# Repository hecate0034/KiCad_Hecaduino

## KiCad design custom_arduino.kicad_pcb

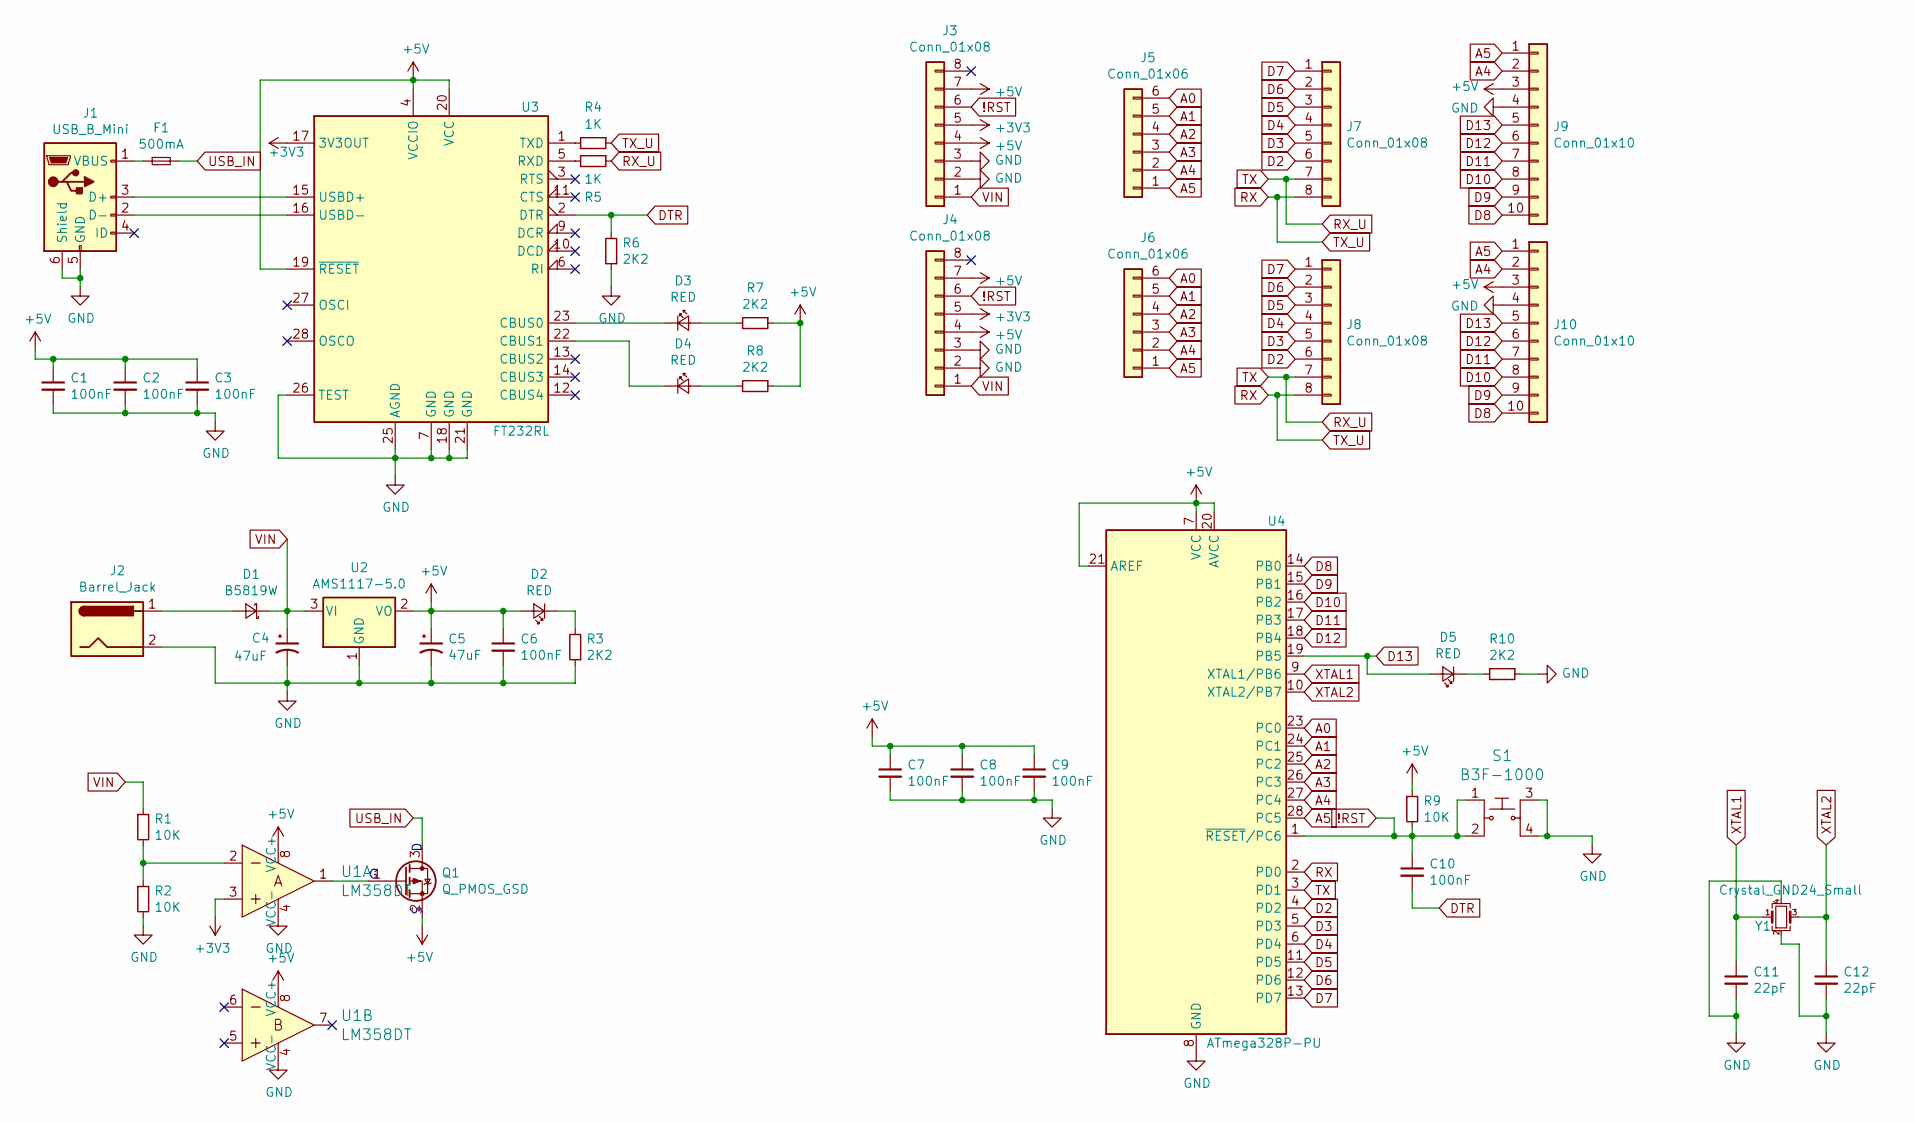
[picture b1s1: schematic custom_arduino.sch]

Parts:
C1, C2, C3, C6, C7, C8, C9, C10: 100nF; C_0402_1005Metric
C4, C5: 47uF; CP_Elec_5x5.4
C11, C12: 22pF; C_0402_1005Metric
D1: B5819W; D_SOD-123
D2, D3, D4, D5: RED; LED_0603_1608Metric
F1: 500mA; Fuse_0603_1608Metric
J1: USB_B_Mini; USB_Mini-B_Lumberg_2486_01_Horizontal
J2: Barrel_Jack; BarrelJack_Horizontal
J3, J4, J7, J8: Conn_01x08; PinSocket_1x08_P2.54mm_Vertical
J5, J6: Conn_01x06; PinSocket_1x06_P2.54mm_Vertical
J9, J10: Conn_01x10; PinSocket_1x10_P2.54mm_Vertical
Q1: Q_PMOS_GSD; SOT-23
R1, R2, R9: 10K; R_0603_1608Metric
R3, R6, R7, R8, R10: 2K2; R_0603_1608Metric
R4, R5: 1K; R_0603_1608Metric
S1: B3F-1000; B3F1002; MPN B3F-1000; Digi-Key_PN SW400-ND
U1: LM358DT; SOIC-8_3.9x4.9mm_P1.27mm; MPN LM358DT; Digi-Key_PN 497-1591-1-ND
U2: AMS1117-5.0; SOT-223-3_TabPin2
U3: FT232RL; SSOP-28_5.3x10.2mm_P0.65mm
U4: ATmega328P-PU; DIP-28_W7.62mm
Y1: Crystal_GND24_Small; Crystal_SMD_3225-4Pin_3.2x2.5mm

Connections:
!RST: C10.1, J3.6, J4.6, R9.2, S1.1, S1.2, U4.1 (~RESET~/PC6)
+3V3: J3.5, J4.5, U1.3, U3.17 (3V3OUT)
+5V: C1.1, C2.1, C3.1, C5.1, C6.1, C7.1, C8.1, C9.1, D2.2 (A), J3.4, J3.7, J4.4, J4.7, J9.3, J10.3, Q1.2 (S), R7.1, R8.1, R9.1, U1.8 (VCC+), U2.2 (VO), U3.4 (VCCIO), U3.19 (~RESET~), U3.20 (VCC), U4.7 (VCC), U4.20 (AVCC), U4.21 (AREF)
A0: J5.6, J6.6, U4.23 (PC0)
A1: J5.5, J6.5, U4.24 (PC1)
A2: J5.4, J6.4, U4.25 (PC2)
A3: J5.3, J6.3, U4.26 (PC3)
A4: J5.2, J6.2, J9.2, J10.2, U4.27 (PC4)
A5: J5.1, J6.1, J9.1, J10.1, U4.28 (PC5)
D2: J7.6, J8.6, U4.4 (PD2)
D3: J7.5, J8.5, U4.5 (PD3)
D4: J7.4, J8.4, U4.6 (PD4)
D5: J7.3, J8.3, U4.11 (PD5)
D6: J7.2, J8.2, U4.12 (PD6)
D7: J7.1, J8.1, U4.13 (PD7)
D8: J9.10, J10.10, U4.14 (PB0)
D9: J9.9, J10.9, U4.15 (PB1)
D10: J9.8, J10.8, U4.16 (PB2)
D11: J9.7, J10.7, U4.17 (PB3)
D12: J9.6, J10.6, U4.18 (PB4)
D13: D5.2 (A), J9.5, J10.5, U4.19 (PB5)
DTR: C10.2, R6.2, U3.2 (DTR)
GND: C1.2, C2.2, C3.2, C4.2, C5.2, C6.2, C7.2, C8.2, C9.2, C11.2, C12.2, J1.5 (GND), J1.6 (Shield), J2.2, J3.2, J3.3, J4.2, J4.3, J9.4, J10.4, R2.2, R3.1, R6.1, R10.1, S1.3, S1.4, U1.4 (VCC-), U2.1 (GND), U3.7 (GND), U3.18 (GND), U3.21 (GND), U3.25 (AGND), U3.26 (TEST), U4.8 (GND), U4.22 (GND), Y1.2, Y1.4
unnamed: D1.2 (A), J2.1
unnamed: D2.1 (K), R3.2
unnamed: D3.1 (K), U3.23 (CBUS0)
unnamed: D3.2 (A), R7.2
unnamed: D4.1 (K), U3.22 (CBUS1)
unnamed: D4.2 (A), R8.2
unnamed: D5.1 (K), R10.2
unnamed: F1.1, J1.1 (VBUS)
unnamed: J1.2 (D-), U3.16 (USBD-)
unnamed: J1.3 (D+), U3.15 (USBD+)
unnamed: Q1.1 (G), U1.1
unnamed: R1.2, R2.1, U1.2
unnamed: R4.2, U3.1 (TXD)
unnamed: R5.2, U3.5 (RXD)
RX: J7.8, J8.8, R4.1, U4.2 (PD0)
RX_U: J7.7, J8.7, R5.1, U4.3 (PD1)
USB_IN: F1.2, Q1.3 (D)
VIN: C4.1, D1.1 (K), J3.1, J4.1, R1.1, U2.3 (VI)
XTAL1: C11.1, U4.9 (XTAL1/PB6), Y1.1
XTAL2: C12.1, U4.10 (XTAL2/PB7), Y1.3

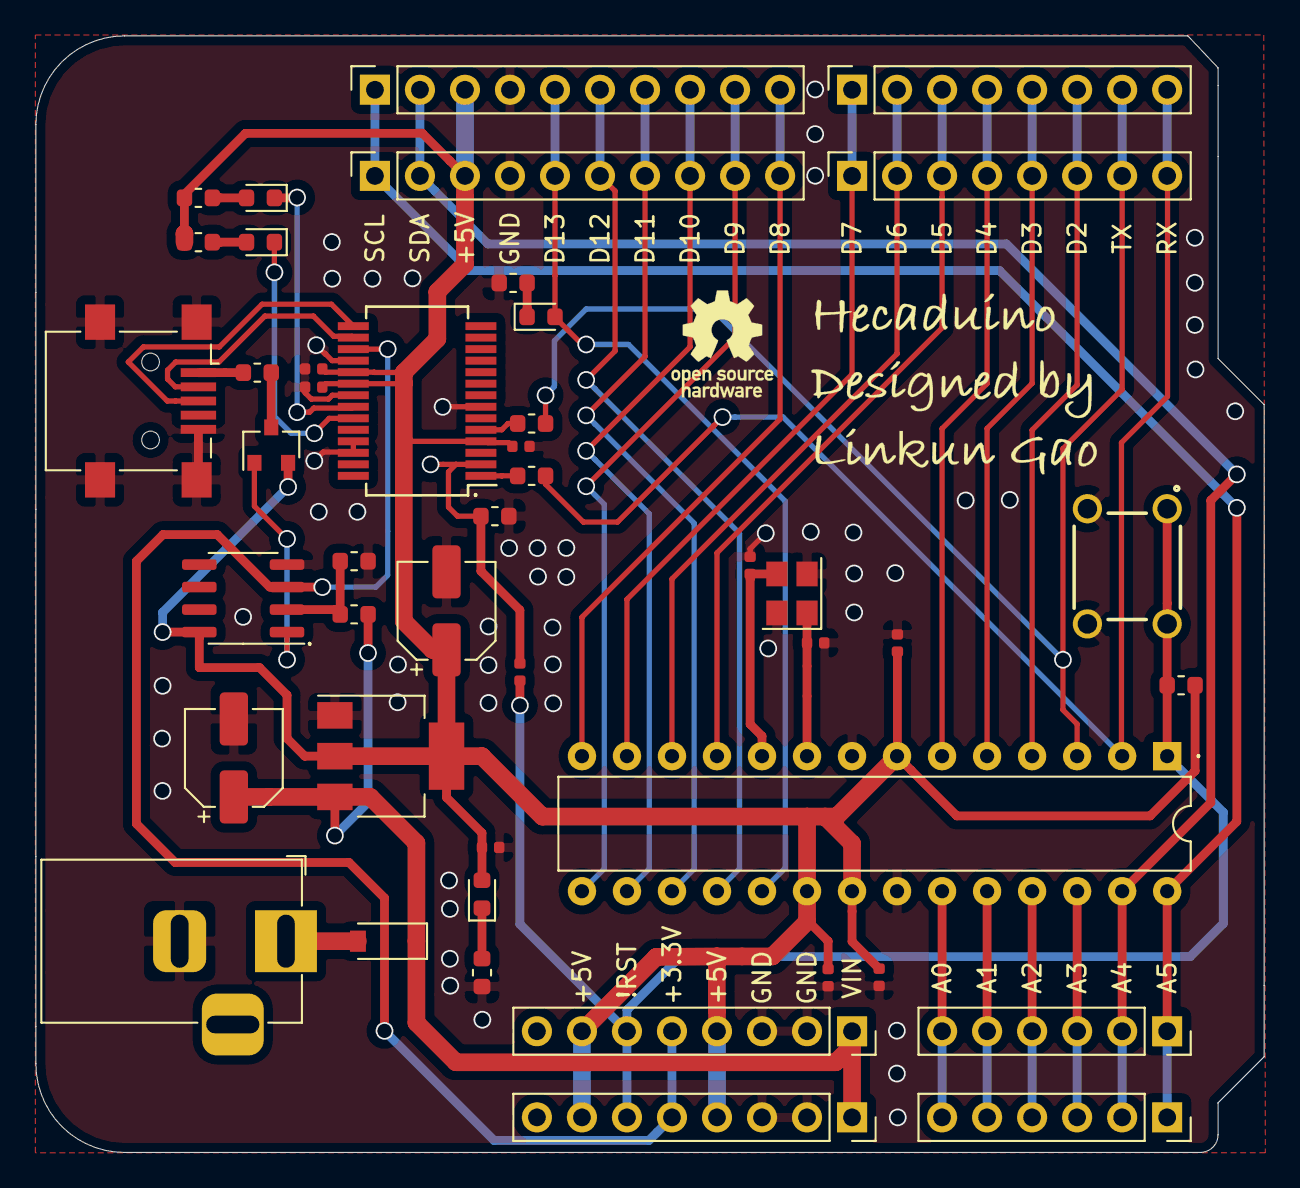
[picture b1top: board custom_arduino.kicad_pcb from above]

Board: 2 copper layers, 69.3 x 63.0 mm, 45 parts (0 on the bottom side), 43 nets.

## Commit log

2020-05-21 Round a corner and move a capacitor away from DC jack
